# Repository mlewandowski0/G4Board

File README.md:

# G4Board
devboard with new G431 stm32 microcontroller

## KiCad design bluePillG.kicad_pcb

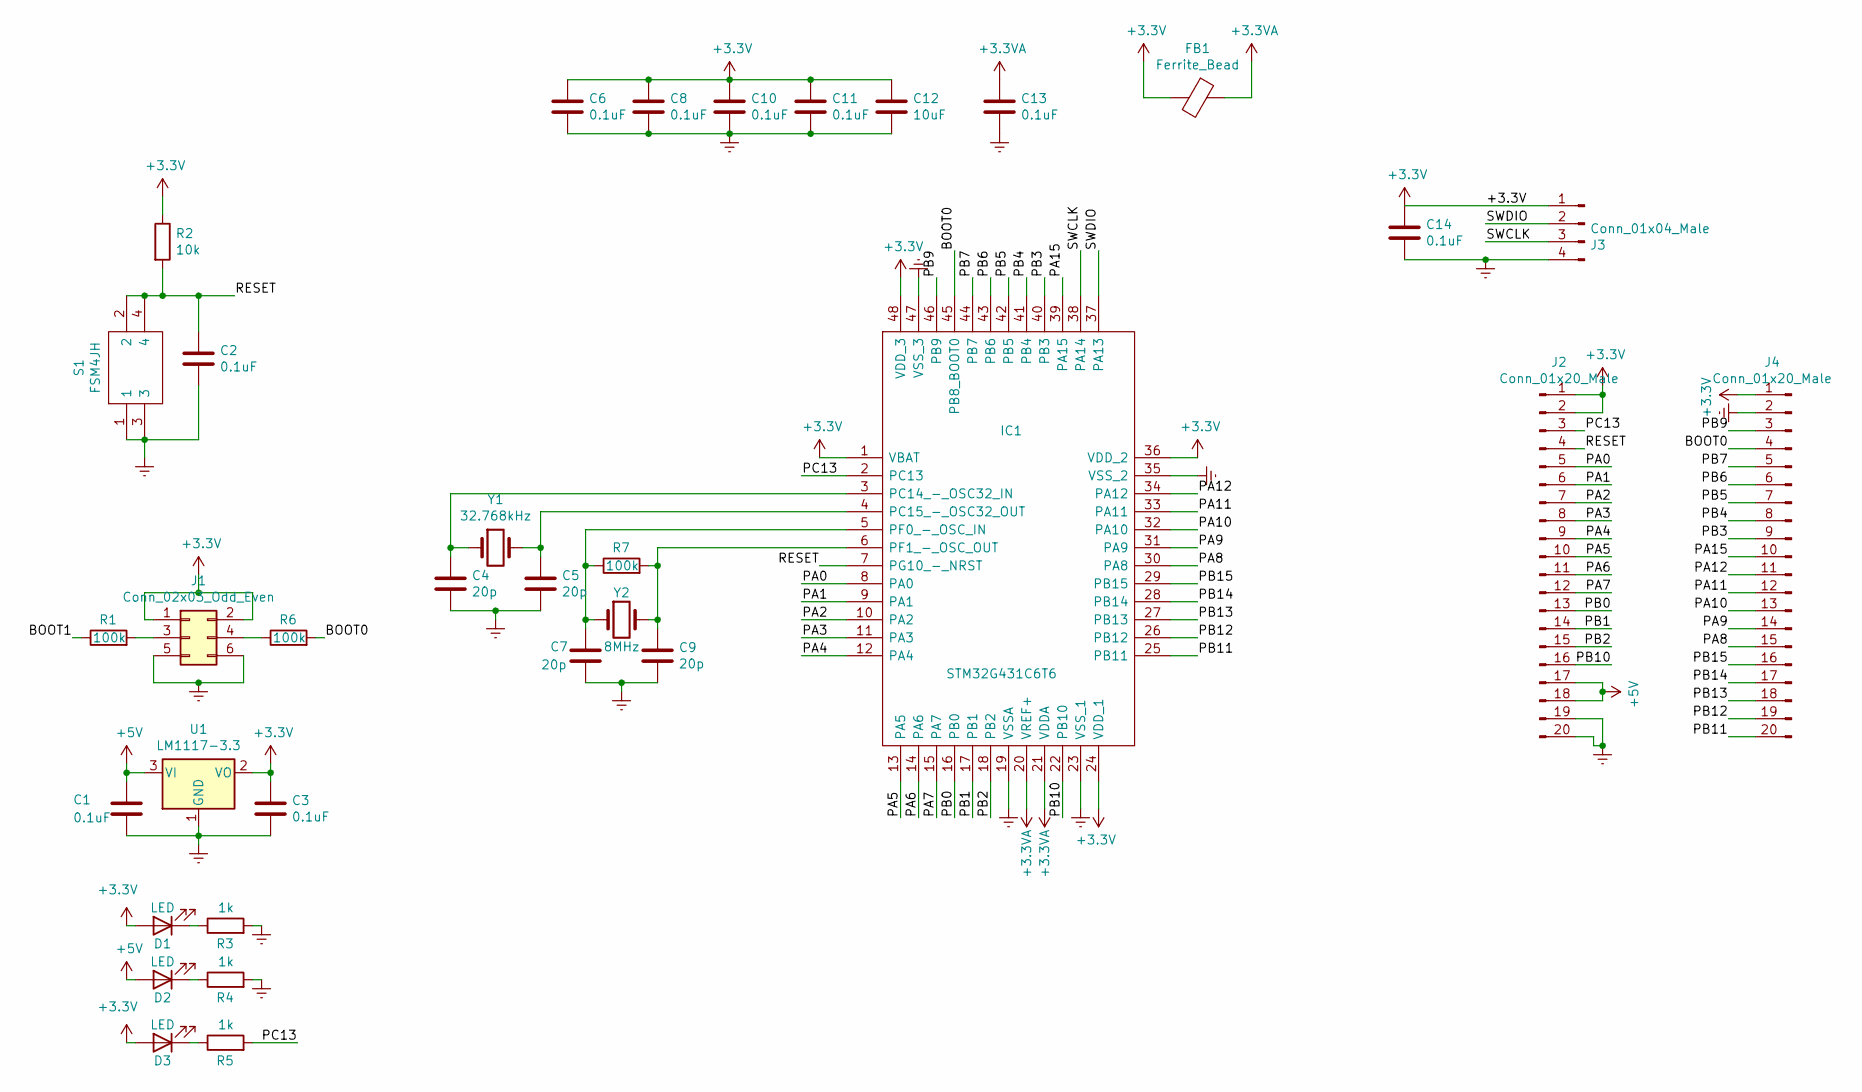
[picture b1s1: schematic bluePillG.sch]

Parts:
C1, C2, C3, C6, C8, C10, C11, C13, C14: 0.1uF; C_0603_1608Metric
C4, C5, C7, C9: 20p; C_0603_1608Metric
C12: 10uF; C_0603_1608Metric
D1, D2, D3: LED; LED_0603_1608Metric
FB1: Ferrite_Bead; R_0805_2012Metric
IC1: STM32G431C6T6; QFP50P900X900X160-48N; Manufacturer_Part_Number STM32G431C6T6; Mouser Part Number 511-STM32G431C6T6
J1: Conn_02x03_Odd_Even; PinHeader_2x03_P2.54mm_Vertical
J2, J4: Conn_01x20_Male; PinHeader_1x20_P2.54mm_Vertical
J3: Conn_01x04_Male; PinHeader_1x04_P2.54mm_Horizontal
R1, R6, R7: 100k; R_0603_1608Metric
R2: 10k; R_0603_1608Metric
R3, R4, R5: 1k; R_0603_1608Metric
S1: FSM4JH; Manufacturer_Part_Number FSM4JH; Mouser Part Number 506-FSM4JH
U1: LM1117-3.3; SOT-223-4
Y1: 32.768kHz; Crystal_AT310_D3.0mm_L10.0mm_Horizontal_1EP_style1
Y2: 8MHz; Crystal_SMD_Abracon_ABM7-2Pin_6.0x3.5mm

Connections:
+3.3VA: C13.1, FB1.1, IC1.20 (VREF+), IC1.21 (VDDA)
+3V3: C3.1, C6.1, C8.1, C10.1, C11.1, C12.1, C14.1, D1.2 (A), D3.2 (A), FB1.2, IC1.1 (VBAT), IC1.24 (VDD_1), IC1.36 (VDD_2), IC1.48 (VDD_3), J1.1, J1.2, J2.1, J2.2, J3.1, J4.1, R2.1, U1.2 (VO), U1.4
+5V: C1.1, D2.2 (A), J2.17, J2.18, U1.3 (VI)
/BOOT0: IC1.45 (PB8_BOOT0), J4.4, R6.2
/BOOT1: R1.1
/PA0: IC1.8 (PA0), J2.5
/PA1: IC1.9 (PA1), J2.6
/PA2: IC1.10 (PA2), J2.7
/PA3: IC1.11 (PA3), J2.8
/PA4: IC1.12 (PA4), J2.9
/PA5: IC1.13 (PA5), J2.10
/PA6: IC1.14 (PA6), J2.11
/PA7: IC1.15 (PA7), J2.12
/PA8: IC1.30 (PA8), J4.15
/PA9: IC1.31 (PA9), J4.14
/PA10: IC1.32 (PA10), J4.13
/PA11: IC1.33 (PA11), J4.12
/PA12: IC1.34 (PA12), J4.11
/PA15: IC1.39 (PA15), J4.10
/PB0: IC1.16 (PB0), J2.13
/PB1: IC1.17 (PB1), J2.14
/PB2: IC1.18 (PB2), J2.15
/PB3: IC1.40 (PB3), J4.9
/PB4: IC1.41 (PB4), J4.8
/PB5: IC1.42 (PB5), J4.7
/PB6: IC1.43 (PB6), J4.6
/PB7: IC1.44 (PB7), J4.5
/PB9: IC1.46 (PB9), J4.3
/PB10: IC1.22 (PB10), J2.16
/PB11: IC1.25 (PB11), J4.20
/PB12: IC1.26 (PB12), J4.19
/PB13: IC1.27 (PB13), J4.18
/PB14: IC1.28 (PB14), J4.17
/PB15: IC1.29 (PB15), J4.16
/PC13: IC1.2 (PC13), J2.3, R5.2
/RESET: C2.1, IC1.7 (PG10_-_NRST), J2.4, R2.2, S1.2, S1.4
/SWCLK: IC1.38 (PA14), J3.3
/SWDIO: IC1.37 (PA13), J3.2
Earth: C1.2, C2.2, C3.2, C4.2, C5.2, C6.2, C7.2, C8.2, C9.2, C10.2, C11.2, C12.2, C13.2, C14.2, IC1.19 (VSSA), IC1.23 (VSS_1), IC1.35 (VSS_2), IC1.47 (VSS_3), J1.5, J1.6, J2.19, J2.20, J3.4, J4.2, R3.2, R4.2, S1.1, S1.3, U1.1 (GND), Y1.3
unnamed: C4.1, IC1.3 (PC14_-_OSC32_IN), Y1.1
unnamed: C5.1, IC1.4 (PC15_-_OSC32_OUT), Y1.2
unnamed: C7.1, IC1.5 (PF0_-_OSC_IN), R7.1, Y2.1
unnamed: C9.1, IC1.6 (PF1_-_OSC_OUT), R7.2, Y2.2
unnamed: D1.1 (K), R3.1
unnamed: D2.1 (K), R4.1
unnamed: D3.1 (K), R5.1
unnamed: J1.3, R1.2
unnamed: J1.4, R6.1

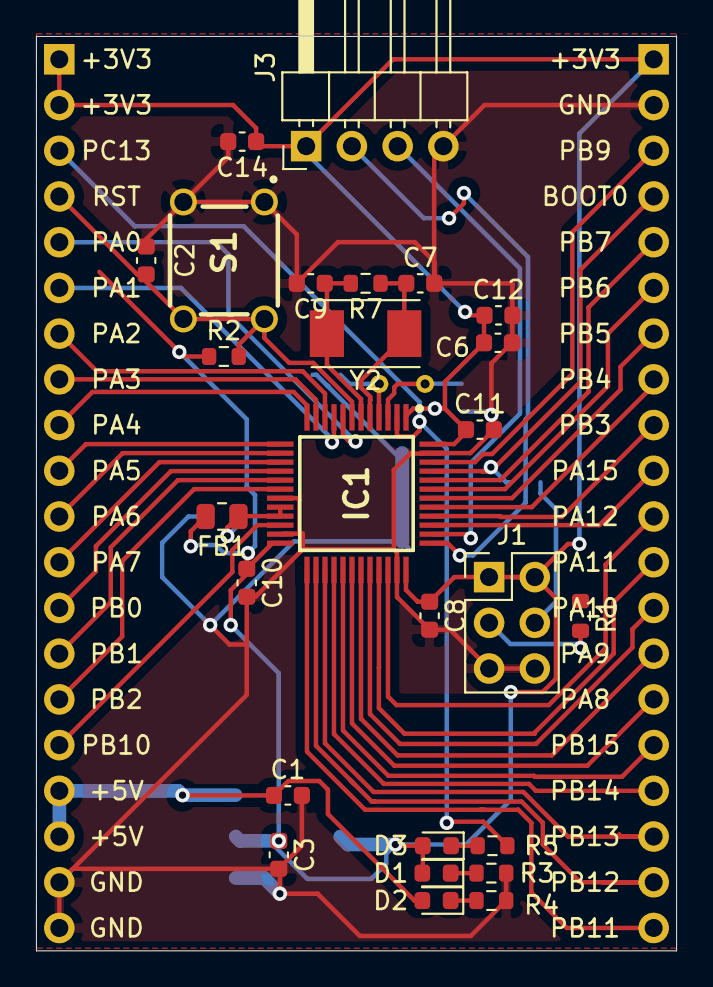
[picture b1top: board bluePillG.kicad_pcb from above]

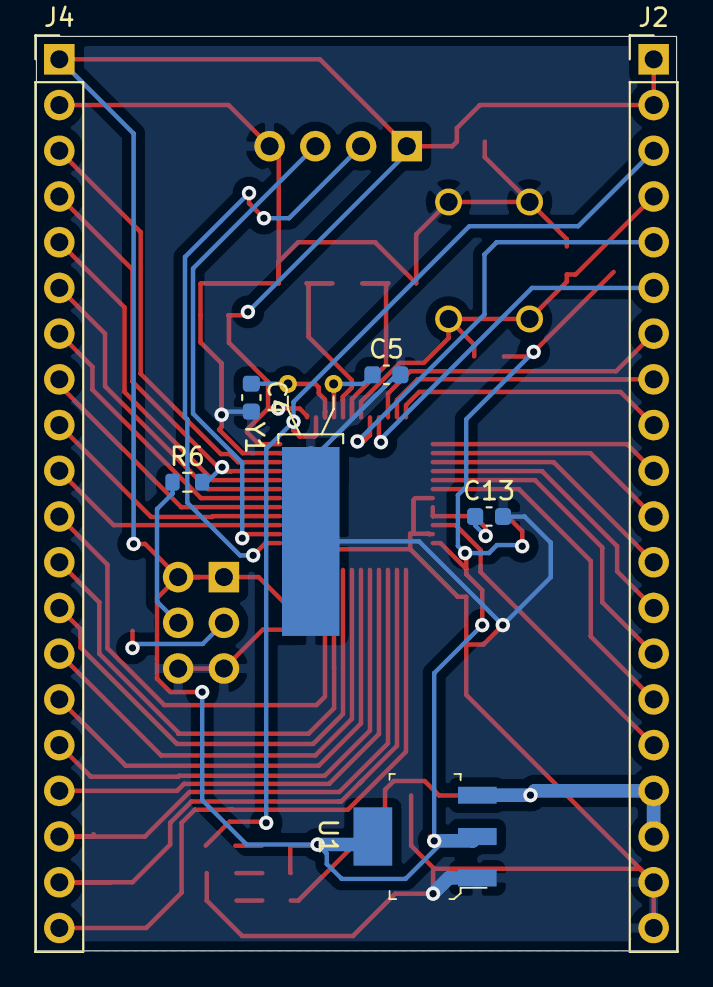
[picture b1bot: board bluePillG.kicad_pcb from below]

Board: 2 copper layers, 35.6 x 50.8 mm, 34 parts (8 on the bottom side), 47 nets.

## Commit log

2021-02-22 cubemx proj
2021-02-22 board
2021-02-23 schematics
2021-03-28 blinker example
2021-03-29 blink
2021-04-16 v2 board schematics
2021-05-02 board v2
2021-05-08 screenshot
